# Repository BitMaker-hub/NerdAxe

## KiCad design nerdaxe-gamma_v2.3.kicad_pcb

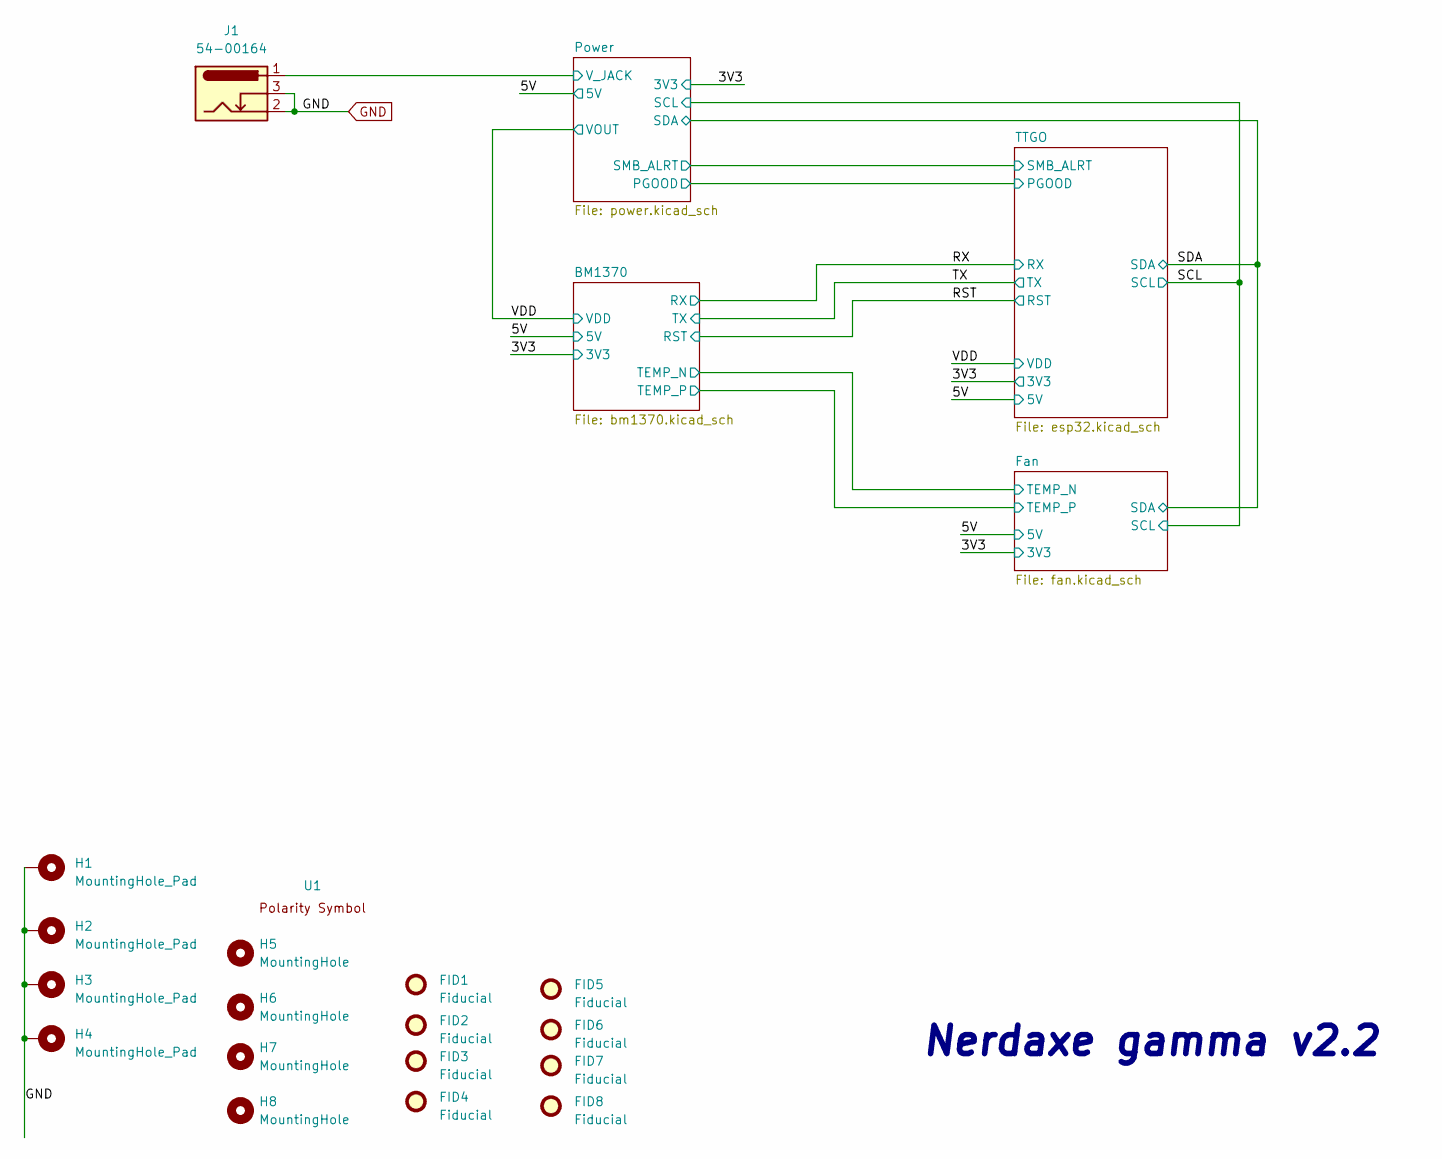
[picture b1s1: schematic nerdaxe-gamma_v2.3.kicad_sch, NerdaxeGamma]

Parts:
FID1, FID2, FID3, FID4, FID5, FID6, FID7, FID8: Fiducial; Fiducial_1mm_Mask2mm
H1, H2, H3, H4: MountingHole_Pad; MountingHole_3mm_Pad_Via
H5, H6, H7, H8: MountingHole; MountingHole_3.5mm
J1: 54-00164; TENSILITY_54-00164; PARTNO 54-00164; LCSC C431534
U1: polarity

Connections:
/Power/V_JACK: J1.1; also elsewhere on the board

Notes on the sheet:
Nerdaxe gamma v2.2

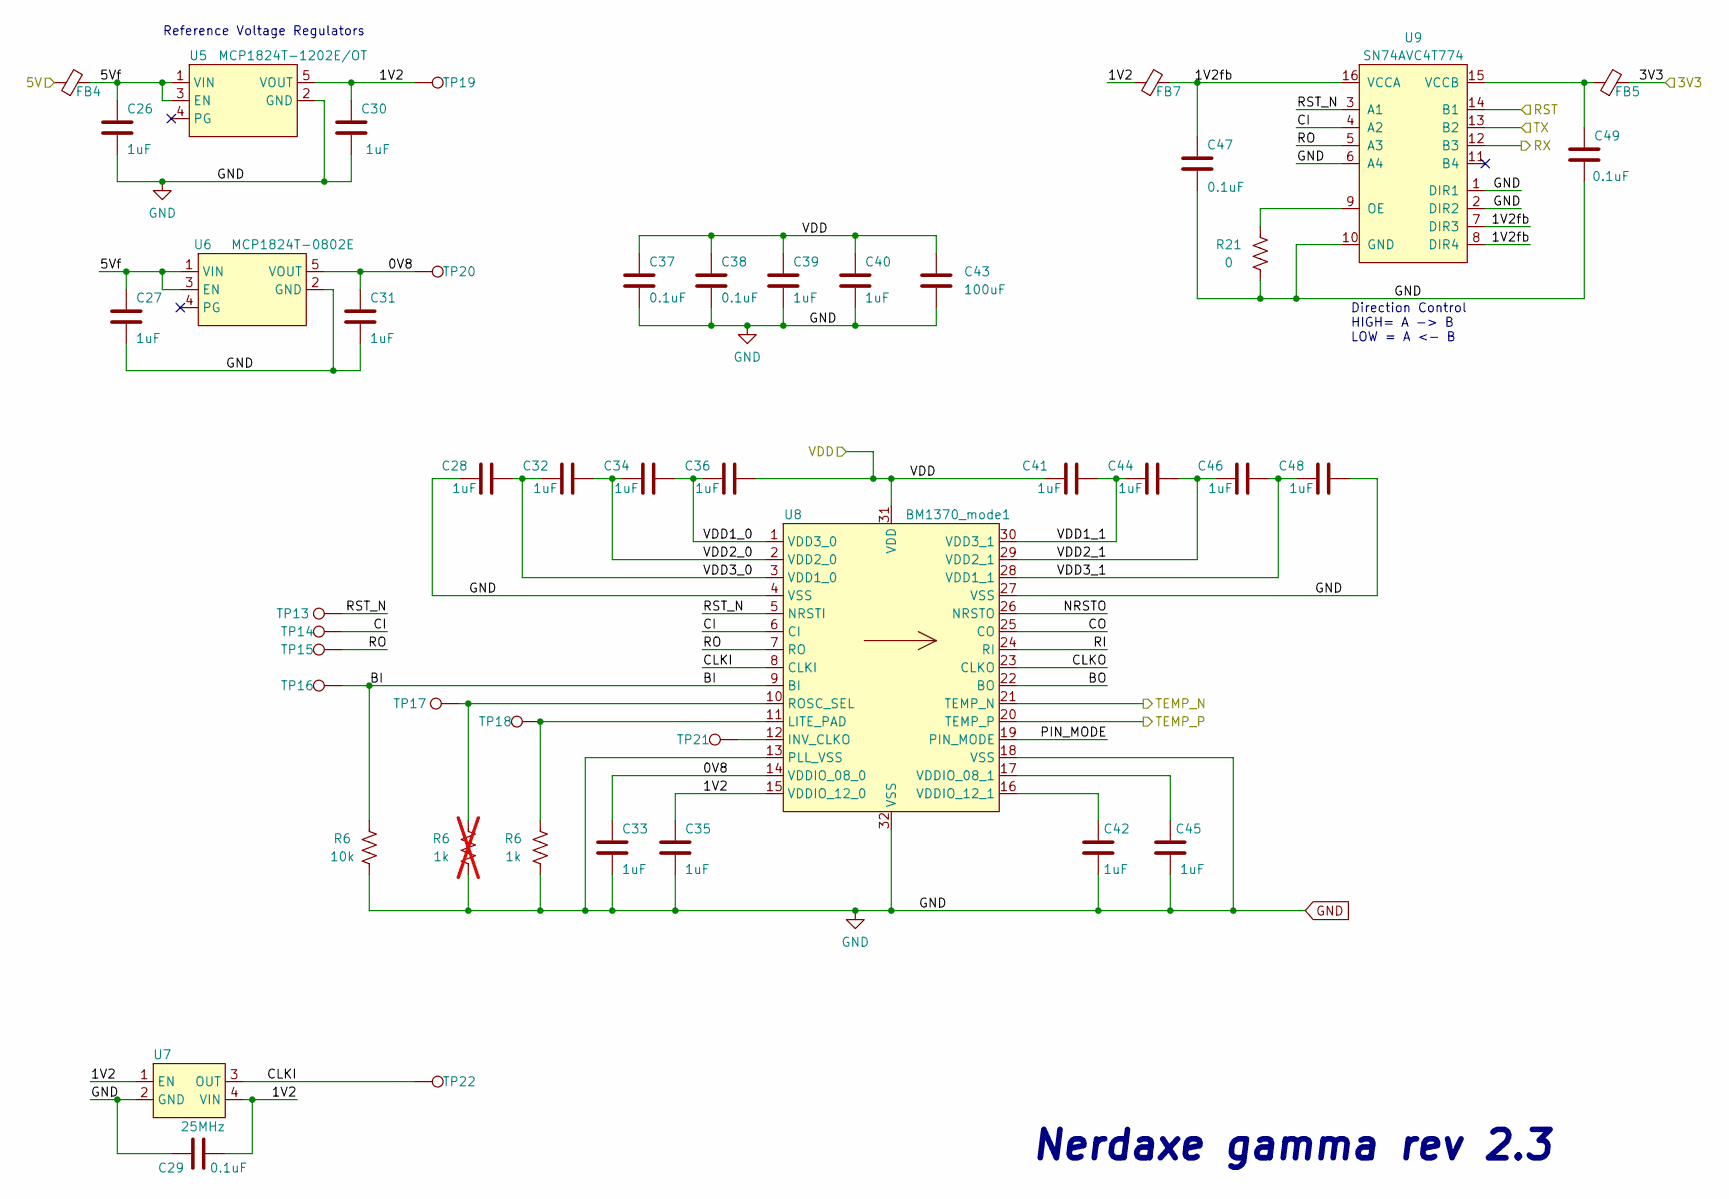
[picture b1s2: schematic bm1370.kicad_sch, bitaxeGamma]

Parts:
C26, C27, C28, C30, C31, C32, C33, C34, C35, C36, C39, C40, C41, C42, C44, C45, C46, C48: 1uF; C_0402_1005Metric; PARTNO EMK105BJ105MV-F
C29, C37, C38, C47, C49: 0.1uF; C_0402_1005Metric; PARTNO CL05A104KO5NNNC
C43: 100uF; C_1206_3216Metric; PARTNO CL31A107MQHNNNE
FB4, FB5, FB7: BLM21PG221SN1D; R_0805_2012Metric
R6: 1k; R_0402_1005Metric; PARTNO RC0402FR-071KL; not fitted
R21: 0; R_0402_1005Metric; PARTNO RC0402FR-0720KL
TP13, TP14, TP15, TP16, TP17, TP18, TP19, TP20, TP21, TP22: TestPoint; TestPoint_Pad_D1.5mm
U5: MCP1824T-1202E/OT; SOT-23-5; PARTNO MCP1824T-1202E/OT
U6: MCP1824T-0802E; SOT-23-5; PARTNO MCP1824T-0802E/OT
U7: 25MHz; SMD3225-4P; PARTNO SX3M25.000E20F30THN; LCSC C5137262
U8: BM1370_mode1; BM1370
U9: SN74AVC4T774; TSSOP-16_4.4x5mm_P0.65mm; PARTNO SN74AVC4T774PWR

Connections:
/3V3: FB5.2; also elsewhere on the board
/5V: FB4.1; also elsewhere on the board
/BM1370/0V8: C31.1, C33.1, TP20.1, U6.5 (VOUT), U8.14 (VDDIO_08_0)
/BM1370/1V2: C29.2, C30.1, C35.1, FB7.1, TP19.1, U5.5 (VOUT), U7.1 (EN), U7.4 (VIN), U8.15 (VDDIO_12_0)
/BM1370/1V2fb: C47.1, FB7.2, U9.7 (DIR3), U9.8 (DIR4), U9.16 (VCCA)
/BM1370/5Vf: C26.1, C27.1, FB4.2, U5.1 (VIN), U5.3 (EN), U6.1 (VIN), U6.3 (EN)
/BM1370/BO: U8.22 (BO)
/BM1370/CI: TP14.1, U8.6 (CI), U9.4 (A2)
/BM1370/CLKI: TP22.1, U7.3 (OUT), U8.8 (CLKI)
/BM1370/CLKO: U8.23 (CLKO)
/BM1370/CO: U8.25 (CO)
/BM1370/NRSTO: U8.26 (NRSTO)
/BM1370/PIN_MODE: U8.19 (PIN_MODE)
/BM1370/RI: U8.24 (RI)
/BM1370/RO: TP15.1, U8.7 (RO), U9.5 (A3)
/BM1370/RST_N: TP13.1, U8.5 (NRSTI), U9.3 (A1)
/BM1370/VDD1_0: C34.2, C36.1, U8.1 (VDD3_0)
/BM1370/VDD1_1: C41.2, C44.1, U8.30 (VDD3_1)
/BM1370/VDD2_0: C32.2, C34.1, U8.2 (VDD2_0)
/BM1370/VDD2_1: C44.2, C46.1, U8.29 (VDD2_1)
/BM1370/VDD3_0: C28.2, C32.1, U8.3 (VDD1_0)
/BM1370/VDD3_1: C46.2, C48.1, U8.28 (VDD1_1)
/Fan/TEMP_N: U8.21 (TEMP_N); also elsewhere on the board
/Fan/TEMP_P: U8.20 (TEMP_P); also elsewhere on the board
/RST: U9.14 (B1); also elsewhere on the board
/RX: U9.12 (B3); also elsewhere on the board
/TX: U9.13 (B2); also elsewhere on the board
/VDD: C36.2, C37.1, C38.1, C39.1, C40.1, C41.1, C43.1, U8.31 (VDD); also elsewhere on the board
unnamed: TP21.1, U8.12 (INV_CLKO)
unnamed: C45.1, U8.17 (VDDIO_08_1)
unnamed: C42.1, U8.16 (VDDIO_12_1)
unnamed: R21.2, U9.9 (OE)
unnamed: C49.1, FB5.1, U9.15 (VCCB)

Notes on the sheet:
Reference Voltage Regulators
Direction Control HIGH= A -> B LOW = A <- B
Nerdaxe gamma rev 2.3

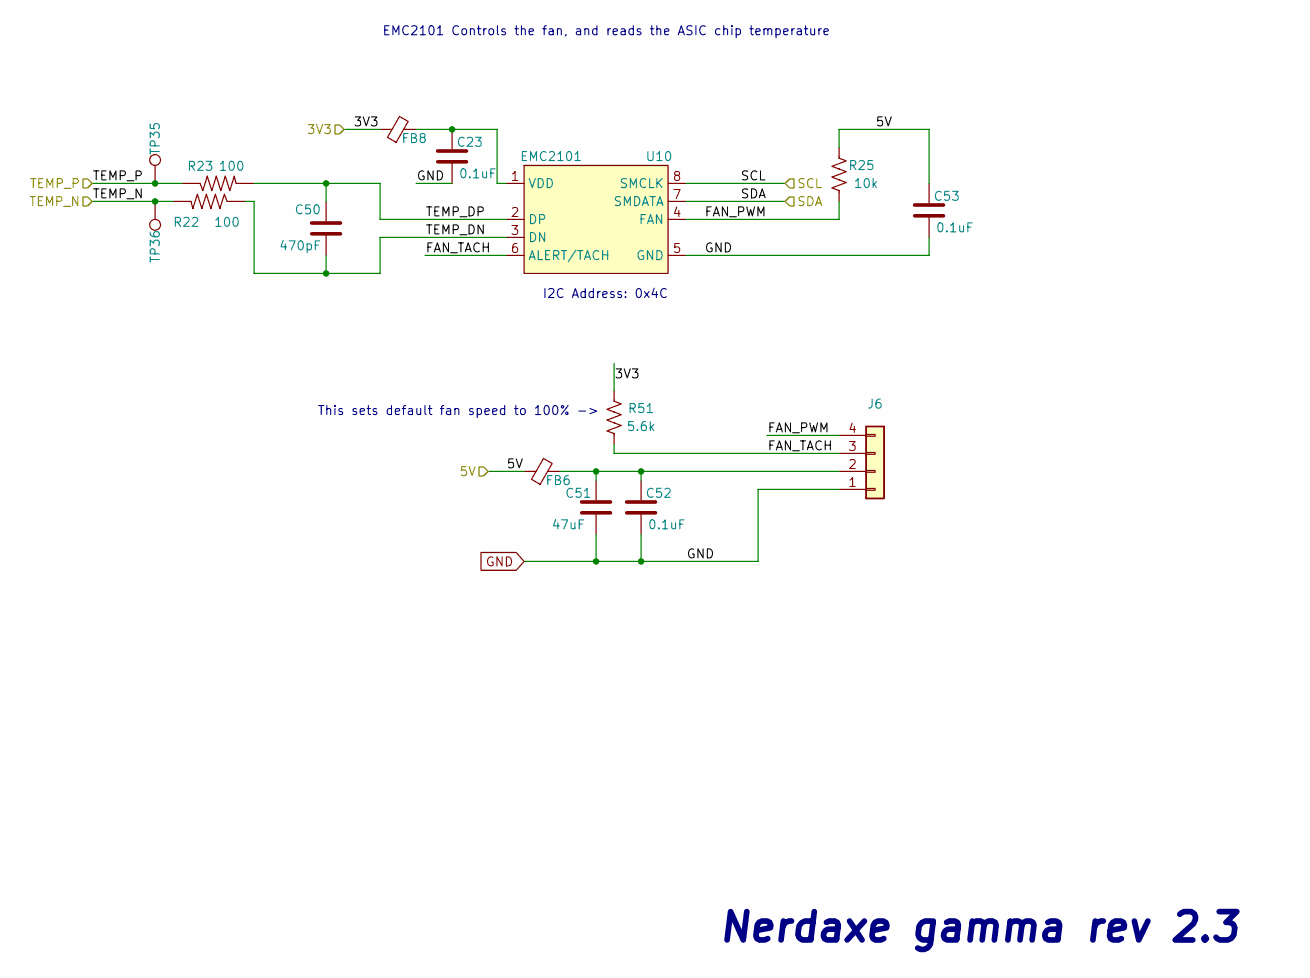
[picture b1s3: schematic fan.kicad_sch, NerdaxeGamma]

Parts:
C23, C52, C53: 0.1uF; C_0402_1005Metric; PARTNO CL05A104KO5NNNC
C50: 470pF; C_0402_1005Metric; PARTNO CL05B471KB5NNNC
C51: 47uF; C_1210_3225Metric; PARTNO CL32A476KOJNNNE
FB6, FB8: BLM21PG221SN1D; R_0805_2012Metric
J6: Conn_01x04; 470531000; PARTNO 0470531000
R22, R23: 100; R_0402_1005Metric; PARTNO RC0402FR-07100RL
R25: 10k; R_0402_1005Metric; PARTNO RC0402JR-0710KL
R51: 5.6k; R_0402_1005Metric; PARTNO RC0402FR-135K6L
TP35, TP36: TestPoint; TestPoint_Pad_D1.5mm
U10: EMC2101; TSSOP-8_3x3mm_P0.65mm; PARTNO EMC2101-R-ACZL-TR

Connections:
/3V3: FB8.1; also elsewhere on the board
/5V: C53.1, FB6.1, R25.2; also elsewhere on the board
/Fan/FAN_PWM: J6.4, R25.1, U10.4 (FAN)
/Fan/FAN_TACH: J6.3, U10.6 (ALERT/TACH); also elsewhere on the board
/Fan/TEMP_DN: C50.2, R22.1, U10.3 (DN)
/Fan/TEMP_DP: C50.1, R23.2, U10.2 (DP)
/Fan/TEMP_N: R22.2, TP36.1; also elsewhere on the board
/Fan/TEMP_P: R23.1, TP35.1; also elsewhere on the board
/SCL: U10.8 (SMCLK); also elsewhere on the board
/SDA: U10.7 (SMDATA); also elsewhere on the board
unnamed: C51.1, C52.1, FB6.2, J6.2
unnamed: C23.1, FB8.2, U10.1 (VDD)

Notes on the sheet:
Nerdaxe gamma rev 2.3
EMC2101 Controls the fan, and reads the ASIC chip temperature
This sets default fan speed to 100% ->
I2C Address: 0x4C

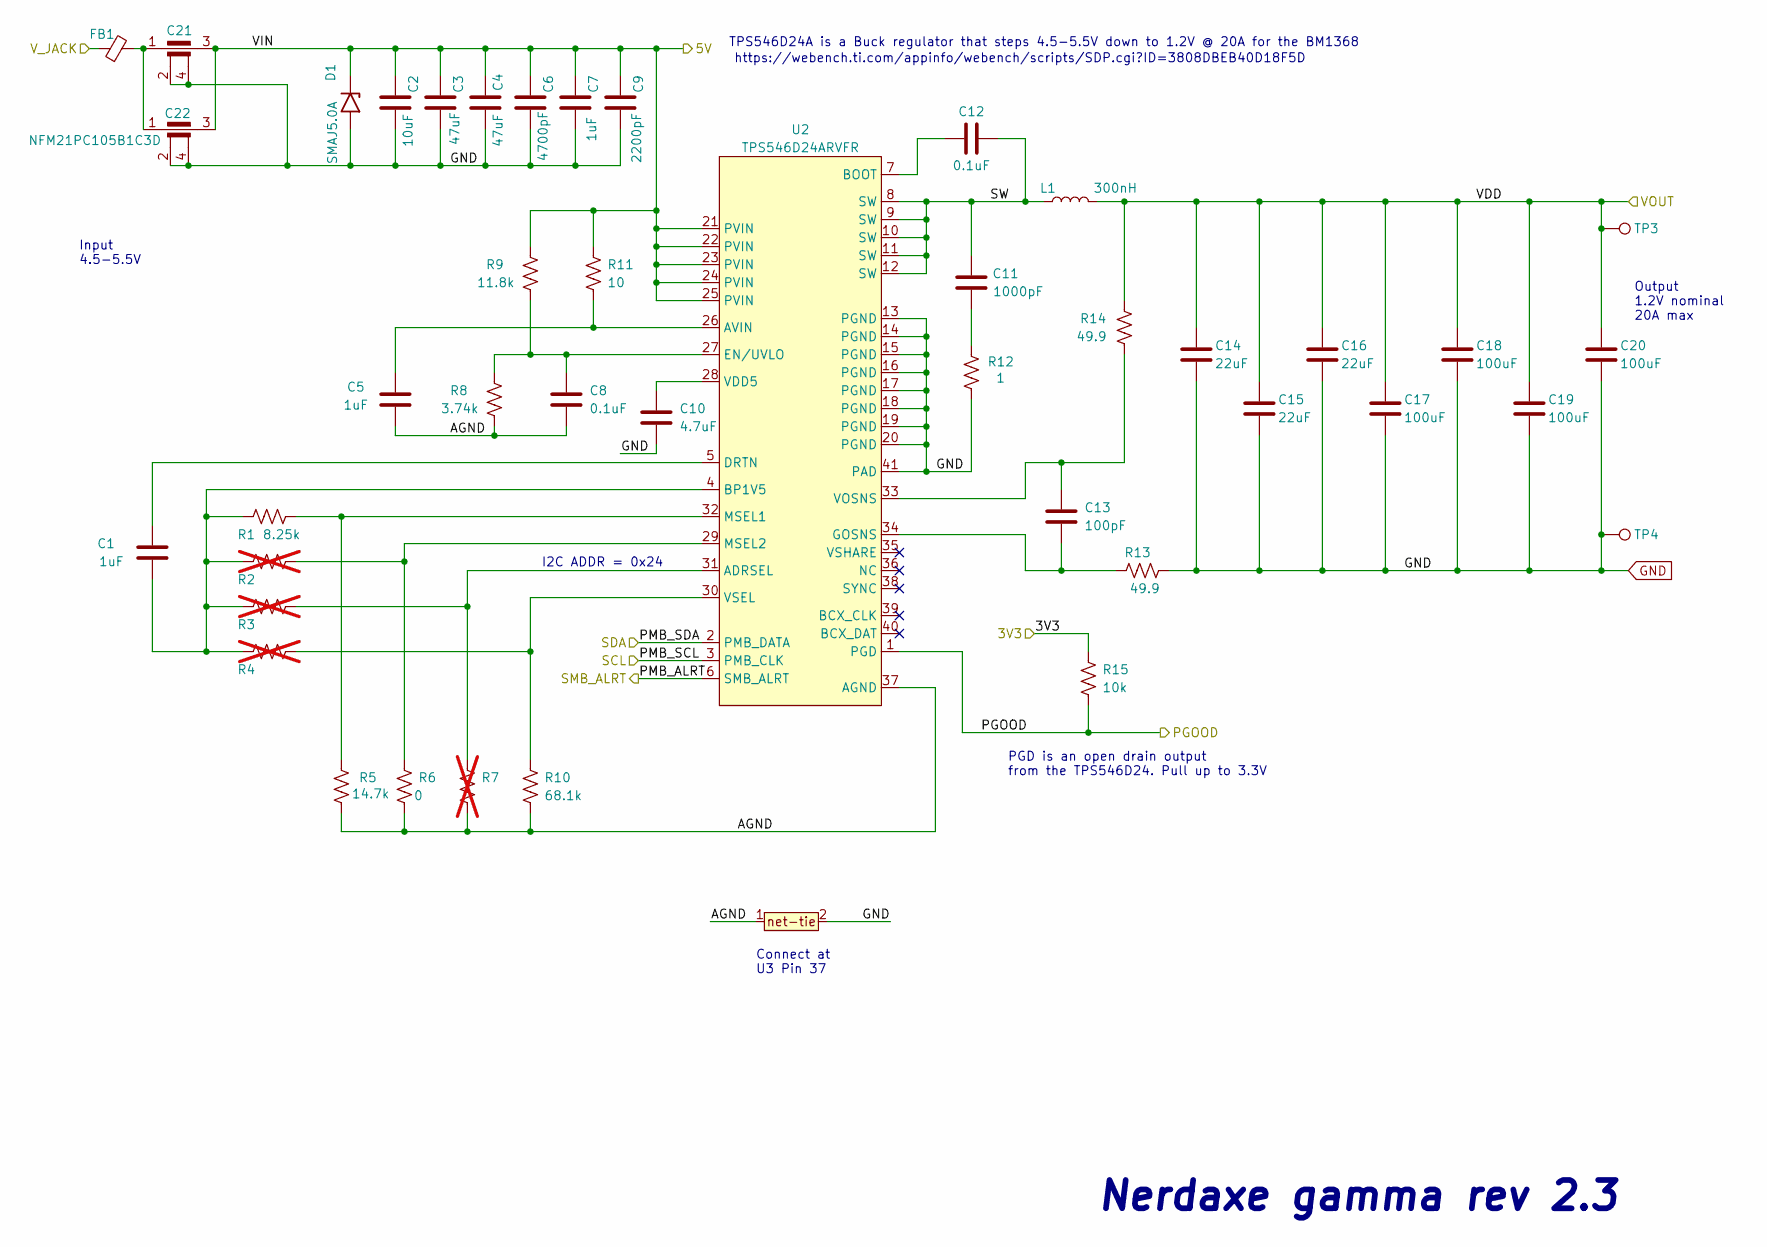
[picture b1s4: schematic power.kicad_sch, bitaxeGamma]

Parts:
C1, C5, C7: 1uF; C_0402_1005Metric; PARTNO EMK105BJ105MV-F
C2: 10uF; C_0805_2012Metric; PARTNO CL21A106KOQNNNE
C3, C4: 47uF; C_1210_3225Metric; PARTNO CL32A476KOJNNNE
C6: 4700pF; C_0402_1005Metric; PARTNO GRM155R71E472KA01D
C8, C12: 0.1uF; C_0402_1005Metric; PARTNO CL05A104KO5NNNC
C9: 2200pF; C_0402_1005Metric; PARTNO GRM155R61H222KA01D
C10: 4.7uF; C_0402_1005Metric; PARTNO GRM155R61A475MEAAD
C11: 1000pF; C_0805_2012Metric; PARTNO CC0805KRX7R9BB102
C13: 100pF; C_0402_1005Metric; PARTNO 885012005013
C14, C15, C16: 22uF; C_0805_2012Metric; PARTNO GRM21BR61A226ME44L
C17, C18, C19, C20: 100uF; C_1206_3216Metric; PARTNO CL31A107MQHNNNE
C21, C22: NFM21PC105B1C3D; NFM21PC105B1C3D_MUR
D1: SMAJ5.0A; D_SMA
FB1: 2508051217Y6; R_0805_2012Metric
L1: 300nH; SLC1175-271MEC_COC; PARTNO SLC1175-301MEC; Mouser 994-SLC1175-271MEC
R1: 8.25k; R_0402_1005Metric; PARTNO RC0402FR-078K25L
R2, R3, R4, R7: R_0402_1005Metric; not fitted
R5: 14.7k; R_0402_1005Metric; PARTNO RC0402FR-0714K7L
R6: 0; R_0402_1005Metric; PARTNO RC0402JR-070RL
R8: 3.74k; R_0402_1005Metric; PARTNO RC0402FR-073K74L
R9: 11.8k; R_0402_1005Metric; PARTNO RC0402FR-0711K8L
R10: 68.1k; R_0402_1005Metric; PARTNO RC0402FR-0768K1L
R11: 10; R_0402_1005Metric; PARTNO RC0402FR-0710RL
R12: 1; R_1206_3216Metric; PARTNO CSR1206FT1R00
R13, R14: 49.9; R_0402_1005Metric; PARTNO RC0402FR-0749R9L
R15: 10k; R_0402_1005Metric; PARTNO RC0402JR-0710KL
T1: net-tie; NetTie-0.25mm
TP3, TP4: TestPoint; TestPoint_Pad_D1.5mm
U2: TPS546D24ARVFR; LQFN40-CLIP; PARTNO TPS546D24ARVFR

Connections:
/3V3: R15.2; also elsewhere on the board
/5V: C2.1, C3.1, C4.1, C6.1, C7.1, C9.1, C21.3, C22.3, D1.1 (A1), R9.1, R11.1, U2.21 (PVIN), U2.22 (PVIN), U2.23 (PVIN), U2.24 (PVIN), U2.25 (PVIN); also elsewhere on the board
/Power/PGOOD: R15.1, U2.1 (PGD); also elsewhere on the board
/Power/PMB_ALRT: U2.6 (SMB_ALRT); also elsewhere on the board
/Power/SW: C11.2, C12.2, L1.1, U2.8 (SW), U2.9 (SW), U2.10 (SW), U2.11 (SW), U2.12 (SW)
/Power/V_JACK: FB1.1; also elsewhere on the board
/SCL: U2.3 (PMB_CLK); also elsewhere on the board
/SDA: U2.2 (PMB_DATA); also elsewhere on the board
/VDD: C14.1, C15.1, C16.1, C17.1, C18.1, C19.1, C20.1, L1.2, R14.1, TP3.1; also elsewhere on the board
unnamed: C11.1, R12.2
unnamed: C21.1, C22.1, FB1.2
unnamed: R3.2, R7.1, U2.31 (ADRSEL)
unnamed: C5.2, R11.2, U2.26 (AVIN)
unnamed: C12.1, U2.7 (BOOT)
unnamed: C1.2, R1.1, R2.1, R3.1, R4.1, U2.4 (BP1V5)
unnamed: C1.1, U2.5 (DRTN)
unnamed: C8.1, R8.1, R9.2, U2.27 (EN/UVLO)
unnamed: C13.2, R13.1, U2.34 (GOSNS)
unnamed: R1.2, R5.2, U2.32 (MSEL1)
unnamed: C10.1, U2.28 (VDD5)
unnamed: C13.1, R14.2, U2.33 (VOSNS)
unnamed: R4.2, R10.1, U2.30 (VSEL)

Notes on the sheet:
TPS546D24A is a Buck regulator that steps 4.5-5.5V down to 1.2V @ 20A for the BM1368
https://webench.ti.com/appinfo/webench/scripts/SDP.cgi?ID=3808DBEB40D18F5D
Input 4.5-5.5V
Nerdaxe gamma rev 2.3
PGD is an open drain output from the TPS546D24. Pull up to 3.3V
I2C ADDR = 0x24
Output 1.2V nominal 20A max
Connect at U3 Pin 37

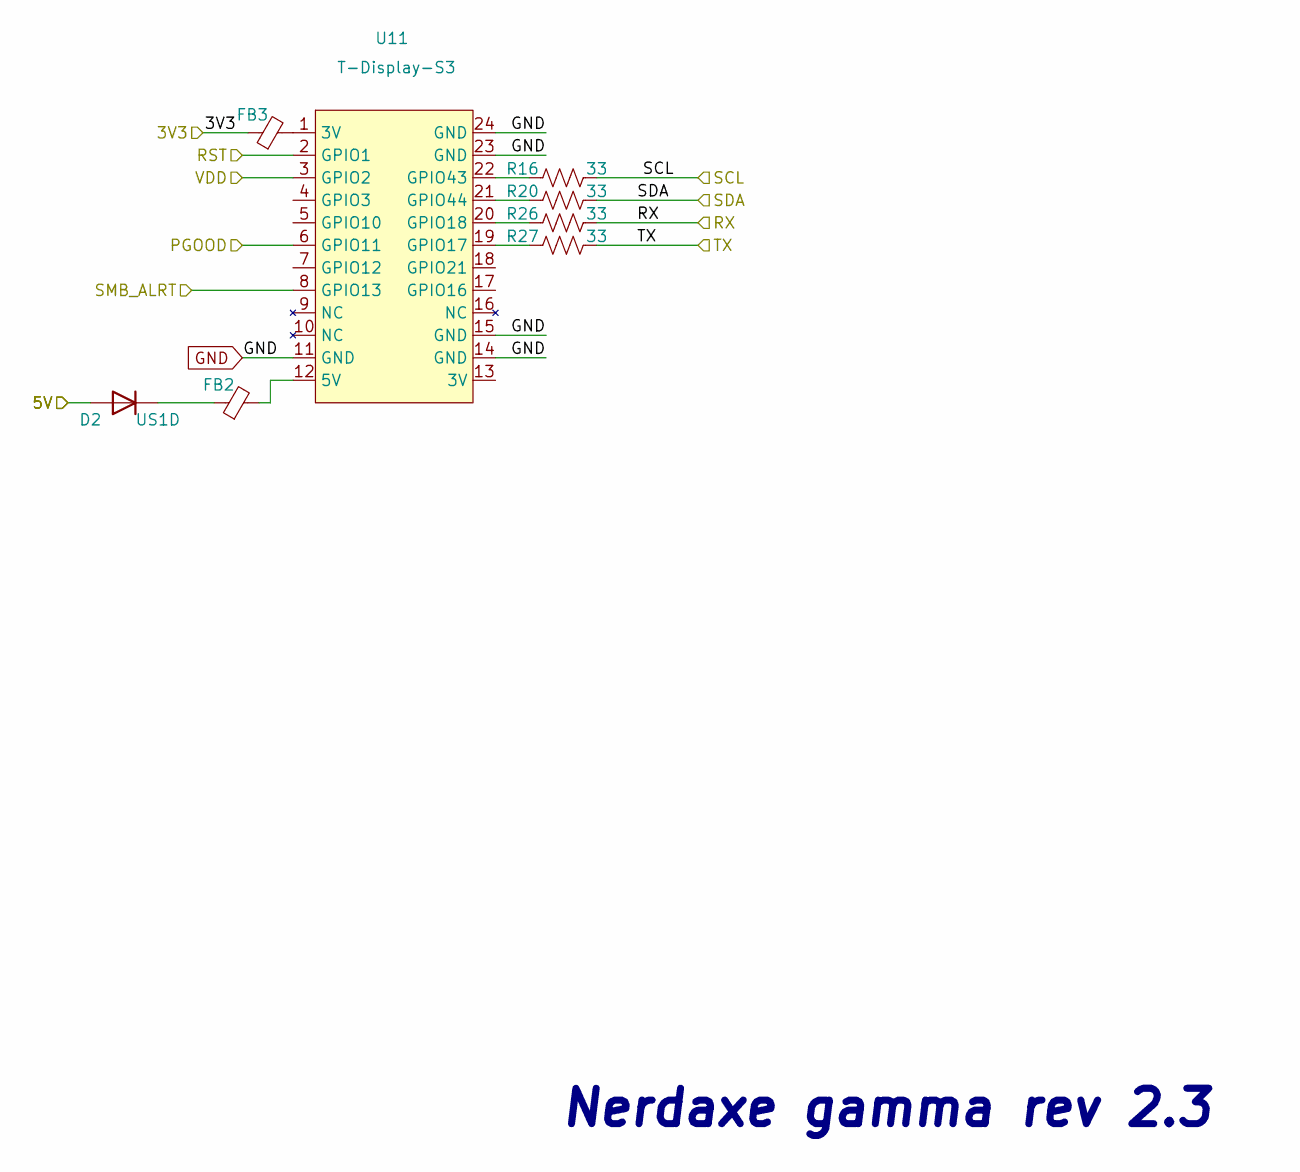
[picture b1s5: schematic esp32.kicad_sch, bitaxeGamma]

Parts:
D2: US1D; D_SMA
FB2: MPZ2012S221A; R_0805_2012Metric
FB3: BLM21PG221SN1D; R_0805_2012Metric
R16, R20, R26, R27: 33; R_0805_2012Metric; PARTNO RC0402FR-0710RL
U11: T-Display-S3

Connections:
/3V3: FB3.1; also elsewhere on the board
/5V: D2.2 (A); also elsewhere on the board
/Power/PGOOD: U11.6 (GPIO11); also elsewhere on the board
/Power/PMB_ALRT: U11.8 (GPIO13); also elsewhere on the board
/RST: U11.2 (GPIO1); also elsewhere on the board
/RX: R26.2; also elsewhere on the board
/SCL: R16.2; also elsewhere on the board
/SDA: R20.2; also elsewhere on the board
/TX: R27.2; also elsewhere on the board
/VDD: U11.3 (GPIO2); also elsewhere on the board
unnamed: D2.1 (K), FB2.1
unnamed: FB3.2, U11.1 (3V)
unnamed: FB2.2, U11.12 (5V)
unnamed: R27.1, U11.19 (GPIO17)
unnamed: R26.1, U11.20 (GPIO18)
unnamed: R16.1, U11.22 (GPIO43)
unnamed: R20.1, U11.21 (GPIO44)

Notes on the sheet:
Nerdaxe gamma rev 2.3

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
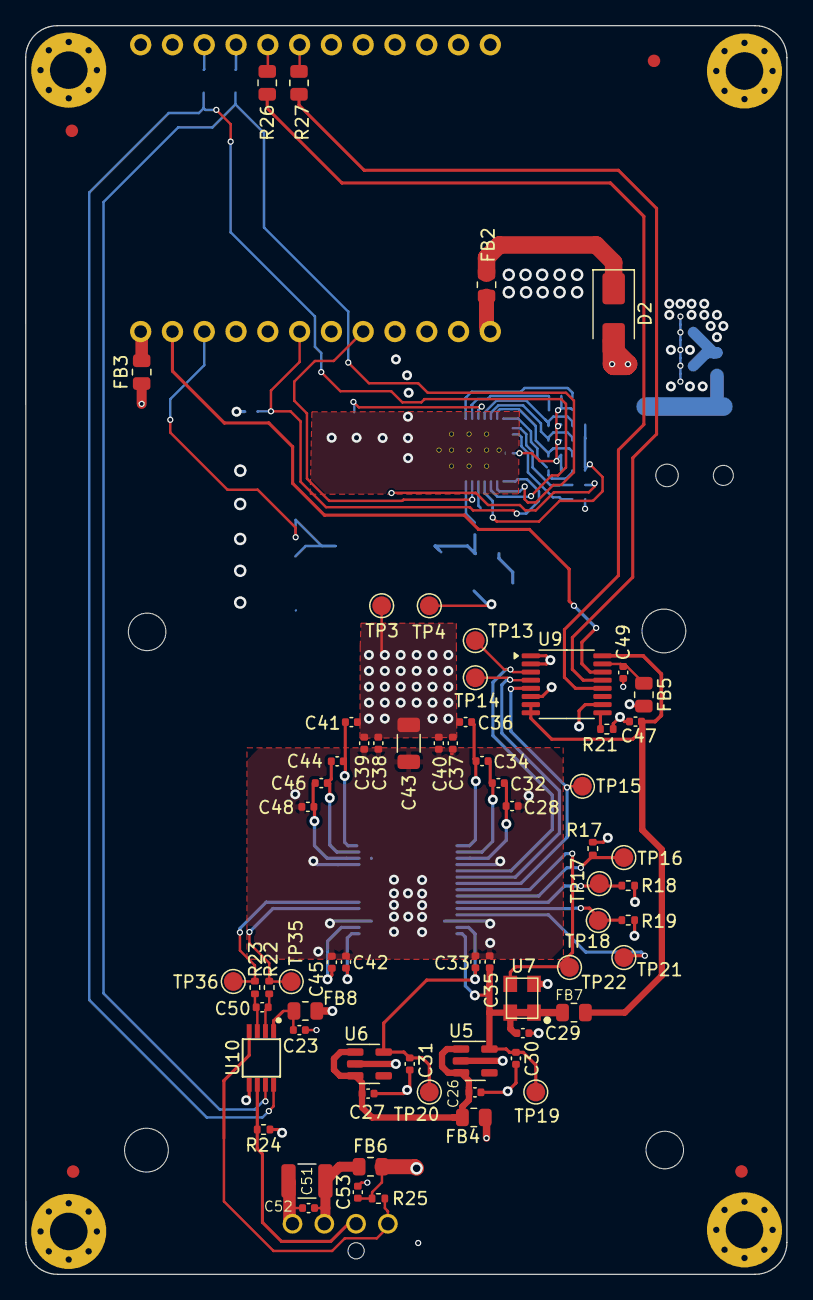
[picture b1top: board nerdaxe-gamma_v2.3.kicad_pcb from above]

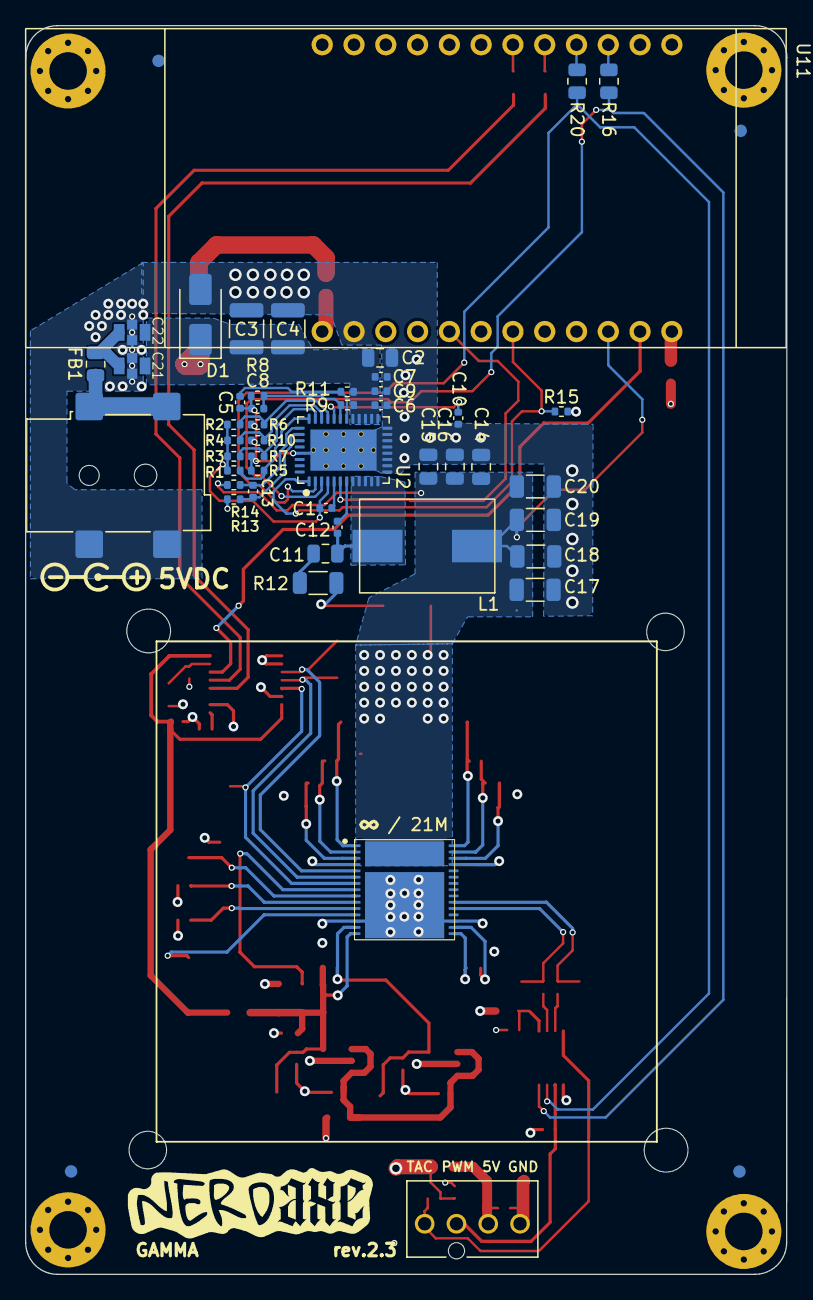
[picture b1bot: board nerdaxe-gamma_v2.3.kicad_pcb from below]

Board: 4 copper layers, 60.8 x 99.8 mm, 131 parts (53 on the bottom side), 65 nets.

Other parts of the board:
R17: 10k; R_0402_1005Metric
R18, R19: 1k; R_0402_1005Metric
R24: 5.6k; R_0402_1005Metric

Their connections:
/3V3: R24.2; also elsewhere on the board
/Fan/FAN_TACH: R24.1; also elsewhere on the board

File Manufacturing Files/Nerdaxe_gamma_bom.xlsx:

Comment | Designator | Footprint | JLCPCB part
4700pF (GRM155R71E472KA01D) | C6 | Condensador 0402 4700PF 25V X7R estándar | C1538
2200pF (GRM155R61H222KA01D) | C9 | Condensador 0402 2200PF 50V X5R | C1531
4.7uF | C10 | Condensador 0402 4.7UF 10V X5R estándar | C191541
1000pF | C11 | Condensador 0805 1000pF 50V estándar | C94121
100pF | C13 | Condensador 0402 100pF/50V XR7 estándar | C281750
470pF | C50 | Condensador 0402 470pF/50V XR7 estándar | C272887
1uF | C1, C5, C7, C26, C27, C28, C30, C31, C32, C33, C34, C35, C36, C39, C40, C41, C4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 | Condensador 0402 1uF 16V XR5 estándar | C113791
22uF (GRM21BR61A226ME44L) | C14, C15, C16 | Condensador 0805 22uF 10V estándar | C29277
100uF (CL31A107MQHNNNE) | C17, C18, C19, C20, C43 | Condensador 1206 100uF 6.3V XR5 estándar | C87164
10uF | C2 | Condensador 0805 10uF 16V XR5 estándar | C89827
47uF (CL32A476KOJNNNE) | C3, C4, C51 | Condensador 1210 47uF 16V XR5 estándar | C412625
0.1uF | C8, C12, C29, C37, C38, C47, C49, C52, C53 | Condensador 0402 100nF 16V estándar | C1525
SMAJ5.0A | D1 | SMAJ5.0A | C113952
US1D | D2 | Diode_SMD:D_SMA | C5140042
Conn_01x04 | J6 | 470531000 | C240840
8.25k | R1 | Resistencia 0402 8.25k estandar | C95598
14.7k | R5 | Resistencia 0402 14k7 1% estandar | C881164
0 | R6, R21 | Resistencia 0402 0ohm estandar | C106231
3.74k | R8 | Resistencia 0402 3.74k 1% estandar | C15172
11.8k | R9 | Resistencia 0402 11.8k 1% estandar | C93752
68.1k | R10 | Resistencia 0402 68.1k 1% estandar | C11537
10 | R11 | Resistencia 0402 10ohm 1% estandar | C25139
1 | R12 | Resistencia 1206 1ohm 1% estandar | C17928
5.6k | R24 | Resistencia 0402 5k6 1% estandar | C365033
49.9 | R13, R14 | Resistencia 0402 49.9 1% estandar | C477760
10k | R15, R17, R25 | Resistencia 0402 10k 1% estandar | C269674
1k | R19 | Resistencia 0402 1k 1% estandar | C11702
100 | R22, R23 | Resistencia 0402 100 1% estandar | C25076
33 | R16, R20, R26, R27 | Resistencia 0805 33 1% estandar | C17634
TPS546D24ARVFR | U2 | TPS546D24ARVFR | C507280
MCP1824T-1202E/OT | U5 | MCP1824T-1202E/OT | C58464
MCP1824T-0802E | U6 | MCP1824T-0802E/OT | C625460
SX3M25.000E20F30THN | U7 | 25MHz - SX3M25.000E20F30THN | C5137262
SN74AVC4T774PWR | U9 | SN74AVC4T774PWR - TSSOP-16 | C129363
EMC2101-R-ACZL-TR | U10 | EMC2101 - TSSOP-8 | C626968
 | Observaciones
 | Muy atentamente,

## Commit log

2025-04-15 Nerdaxe Gamma v2.3
    - Fix Emi CE needs
    - Added ferrite beads + EMI blocking capacitors
    - New components added: R16, R20, R26, R27C21, C22, C23, FB1, FB2, FB3, FB4, FB5, FB6
2025-04-15 revert readme changes
